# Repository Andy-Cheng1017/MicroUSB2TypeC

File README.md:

# MicroUSB2TypeC
這是把普通MicroUSB Footprint轉乘Type-C母座，Type-C購買連結在Symble資訊欄裡面

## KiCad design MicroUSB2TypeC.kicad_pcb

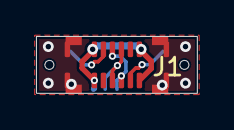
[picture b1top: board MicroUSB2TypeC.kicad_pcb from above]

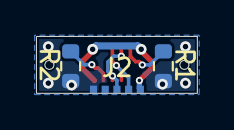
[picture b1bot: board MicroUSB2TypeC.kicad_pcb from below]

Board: 2 copper layers, 8.9 x 3.2 mm, 4 parts (2 on the bottom side), 6 nets.

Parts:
J1: USB_C_Receptacle_USB2.0; Type-C 16P Stand SMD
J2: USB_B_Micro; USB_Micro-B_GCT_USB3076-30-A
R1, R2: 5.1K; R_0603_1608Metric

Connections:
GND: J1.A1 (GND), J1.A12 (GND), J1.B1 (GND), J1.B12 (GND), J1.S1 (SHIELD), J2.5 (GND), R1.1, R2.1
unnamed: J1.A4 (VBUS), J1.A9 (VBUS), J1.B4 (VBUS), J1.B9 (VBUS), J2.1 (VBUS)
unnamed: J1.A5 (CC1), R1.2
unnamed: J1.A6 (D+), J1.B6 (D+), J2.3 (D+)
unnamed: J1.A7 (D-), J1.B7 (D-), J2.2 (D-)
unnamed: J1.B5 (CC2), R2.2

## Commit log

2023-04-05 First update
